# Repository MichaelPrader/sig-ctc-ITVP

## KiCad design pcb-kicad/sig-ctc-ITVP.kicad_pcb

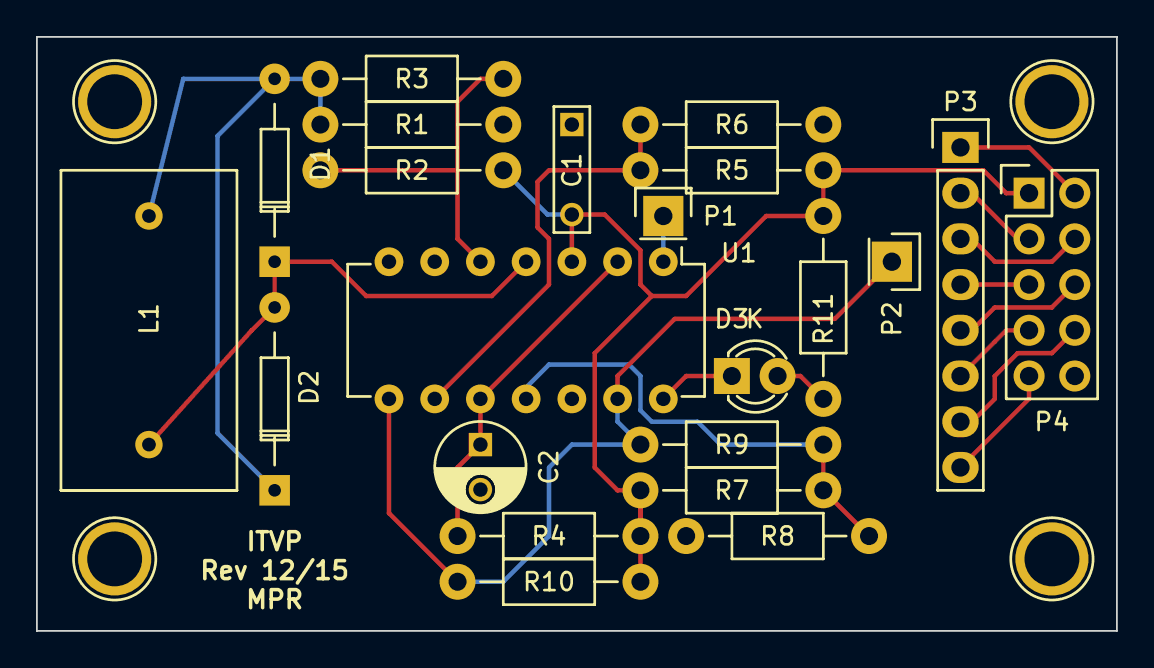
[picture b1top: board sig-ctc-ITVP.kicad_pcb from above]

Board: 2 copper layers, 60.0 x 33.0 mm, 22 parts (0 on the bottom side), 20 nets.

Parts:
C1: 100nF; C_Rect_L7_W2_P5
C2: 1uF; C_Radial_D5_L6_P2.5
D1, D2: 1N4001; Diode_DO-35_SOD27_Horizontal_RM10
D3: LED; LED-3MM
L1: INDUCTOR; CST306-3A
P1, P2: Selector; Pin_Header_Straight_1x01
P3: Selector 0-7; Pin_Header_Straight_1x08
P4: BUS; Pin_Header_Straight_2x05
R1: 4.3k; Resistor_Horizontal_RM10mm
R2: 5.1k; Resistor_Horizontal_RM10mm
R3: 750; Resistor_Horizontal_RM10mm
R4: 750k; Resistor_Horizontal_RM10mm
R5, R9: 10k; Resistor_Horizontal_RM10mm
R6: 10ki; Resistor_Horizontal_RM10mm
R7, R8, R10: 4.7k; Resistor_Horizontal_RM10mm
R11: 1k; Resistor_Horizontal_RM10mm
U1: LM339; DIP-14_W7.62mm

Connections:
+5V: C1.2, P4.1, R2.1, R4.1, R5.1, R7.1, R10.1, R11.1, U1.3
/Out0: P3.1, P4.2
/Out1: P3.2, P4.3
/Out2: P3.3, P4.4
/Out3: P3.4, P4.5
/Out4: P3.5, P4.6
/Out5: P3.6, P4.7
/Out6: P3.7, P4.8
/Out7: P3.8, P4.9
GND: C1.1, C2.2, P4.10, R1.2, R6.2, R8.2, U1.6, U1.7, U1.12
unnamed: C2.1, R4.2, U1.2, U1.10
unnamed: D1.1, D2.2, L1.1, U1.4
unnamed: D1.2, D2.1, L1.2, R1.1, R3.2
unnamed: D3.1, U1.14
unnamed: D3.2, R11.2
unnamed: P1.1, U1.1
unnamed: P2.1, R9.1, R10.2, U1.8, U1.13
unnamed: R2.2, R3.1, U1.5
unnamed: R5.2, R6.1, U1.9
unnamed: R7.2, R8.1, R9.2, U1.11
